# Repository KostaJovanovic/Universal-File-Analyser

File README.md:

## Download the apps

[Download stable release](https://github.com/KostaJovanovic/Universal-File-Analyser/releases/latest)

<div align="center">

# Analyser

**A zero-backend forensic workbench for files, running entirely in your browser.**

Drop in any file and it is classified, parsed and visualised on your device. Nothing is uploaded, ever.

[**Open Analyser**](https://analyser.valjdakosta.com) · [Supported formats](https://analyser.valjdakosta.com/formats) · [Samples](https://analyser.valjdakosta.com/samples) · [About](https://analyser.valjdakosta.com/about) · [Changelog](https://analyser.valjdakosta.com/patch)

</div>

---

## Download the apps

[Download stable release](https://github.com/KostaJovanovic/Universal-File-Analyser/releases/latest)

## Why

Most "file inspector" sites work by uploading your file to a server, which is exactly what you do not want for private photos, contracts, disk images or key files. Analyser takes the opposite approach: the page is static, there is no backend at all, and every byte of analysis happens in your browser through the File API and lazy-loaded WebAssembly. It works offline as an installable PWA, and you can verify the no-upload claim with the network tab open.

## What it can open

Analyser recognises **over 1,350 file types**. The depth varies by format: photos, audio, video, documents, 3D models, archives, maps and databases get full viewers and deep analysis, while hundreds of proprietary formats are identified by magic bytes with their header metadata decoded. Anything still unknown gets a hex dump and best-effort identification.

The full, searchable list is at [analyser.valjdakosta.com/formats](https://analyser.valjdakosta.com/formats), with a guide page for every supported extension. There is also a [compare page](https://analyser.valjdakosta.com/compare) that runs two files through the same analysis side by side and highlights every field where they differ, and a [samples gallery](https://analyser.valjdakosta.com/samples) of example files to try without needing your own.

## Beyond identification

Identifying a file is just the entry point. The real work starts once Analyser knows what it is holding, and a lot of that is best shown rather than described.

### Audio: spectrograms, isolation and on-device AI

Waveform and spectrogram views (down into the sub-20 Hz range), codec and loudness analysis, reversed playback, and live microphone capture. The frequency-isolation panel lets you carve out bands in real time, and an in-browser AI model separates vocals from instrumentals with no server round-trip.

<div align="center">

</div>

<div align="center">

https://github.com/user-attachments/assets/a9226e4a-90d0-45d2-8c82-d65578e2b3e8

<em>On-device AI vocal separation: the model runs entirely in the browser, nothing is uploaded.</em>

</div>

### 3D, CAD and manufacturing

STL and STEP/IGES viewers, DWG drawings, SolidWorks and Fusion 360 packages, and a G-code toolpath simulator that rebuilds the print as solid deposited filament, animates the build layer by layer, and can export a shareable video clip of it.

<div align="center">

</div>

### Electronics

KiCad and Altium PCB projects render as an interactive 3D board you can flip and inspect, alongside schematics, SPICE waveforms and IPC netlists.

<div align="center">

</div>

### Creative project files

After Effects, Premiere, DaVinci Resolve and VEGAS projects with previewable composition timelines, EDL/FCPXML/OTIO timelines, PSD and Illustrator files, colour LUTs, animated font specimens, Lottie animations, MIDI scores, subtitles and lyrics.

<div align="center">

</div>

### Folders and archives

Browse ZIP, 7z, RAR and whole dropped folders, with a treemap that breaks down where the size actually goes and lets you click straight into any file to analyse it. Comics (CBZ/CBR), e-books (EPUB/MOBI), DjVu scans and Jupyter notebooks get proper readers.

<div align="center">

</div>

### And more

- **File recovery** - repair truncated or corrupt JPEG/PNG files, rebuild a damaged JPEG header using a reference photo from the same camera, carve embedded images out of any blob, and salvage unfinalised MP4/MOV recordings with no index by extracting the raw H.264/H.265 stream (with a reference clip as donor if needed).
- **Photos** - EXIF and GPS readout, histograms, OCR, QR-code detection, HEIC and camera-RAW conversion, and a "sonify" mode that turns the image into sound.
- **Video** - per-frame and stream analysis, scene-change detection, and scrubbing synced between the player and the readouts.
- **Forensics and data** - CRC-32, MD5, SHA-1, SHA-256 and SHA-512 hashes, a network-indicator (OSINT) card that pulls URLs, IPs, domains and emails out of any file into click-to-open lookup links (nothing is contacted automatically), plus viewers for SQLite databases, git objects, emails and disk images, and a JSON export of the full analysis.
- **Geodata** - GPX tracks, KML and GeoJSON plotted on a map, rendered locally.

## Privacy

- No uploads: files are read with the File API and never leave the device.
- No accounts, no trackers, ZERO tracking cookies. The only thing counted is an anonymous per-extension tally (see the privacy page).
- Works fully offline once installed; the service worker precaches the app shell and keeps the WASM engines after first use.
- Private keys and secrets found inside files are flagged, not transmitted.

The only network call the site ever makes on its own is a single anonymous "file analysed" ping carrying nothing but a lowercase extension string. Those counts feed the public [live-usage page](https://analyser.valjdakosta.com/stats), an honest tally of what people drop, with unrecognised types pooled into one row so their names are never shown or stored.

<div align="center">

</div>

## Style

You have probably never seen a file analysis website this stylish. It follows a [swiss design](https://en.wikipedia.org/wiki/Swiss_Style_(design)) inspired layout, colour palette and set of fonts which I am very happy with. I made sure to sacrifice no functionality or readability for the sake of being cool, and hopefully succeeded in that too. Sharp corners, mono type, no clutter. And a... hidden game?

<div align="center">

</div>

## Under the hood

The site is plain HTML, CSS and ES-module JavaScript. No framework, no build step, no `node_modules`. Heavy lifting is done by WebAssembly engines and specialist libraries, loaded lazily only when a file actually needs them:

- **FFmpeg** for video remuxing, frame extraction and audio decoding
- **ImageMagick** for RAW photo conversion
- **pdf.js** and **Ghostscript** for PDF and PostScript
- **Tesseract** for OCR
- **OpenCASCADE** for STEP/IGES tessellation (fetched on first use, then cached for offline)
- **sql.js** for SQLite, **libarchive** and **xz** for archives, **OpenJPEG** for JPEG 2000
- **exifr**, **heic2any**, **jsQR**, **Leaflet**, **fflate** and friends

Most parsing, though, is hand-written: a couple of hundred binary header parsers organised into lazy per-domain chunks, so the initial page stays small. Deployment is just static assets on Cloudflare; every push to `main` ships.

## Offline install

The "Download for offline use" section in the footer caches Analyser as an installable, fully offline Progressive Web App, in three cumulative tiers: **Essentials** (the whole app), **Everything** (adds OCR, maps, QR scanning, HEIC, archives, PostScript, CAD drawings and the samples gallery) and **Complete** (OCR in 30+ languages plus the on-device AI vocal separation).

<div align="center">

</div>

## Desktop app

Analyser also runs as a desktop application for Windows, macOS and Linux. It wraps the same `web/` tree the site serves, so there is no fork of the code and nothing in the analysis pipeline changes - and the privacy promise is identical, since everything still happens on your own machine.

The source is in `desktop/` (Electron, its own `package.json`). Build the Windows installer locally with `cd desktop && npm install && npm run dist`, which writes `Analyser-Windows-<version>.exe` into `desktop/dist/`. That one file installs Analyser or unpacks a portable copy. The desktop adds File > Open and Open folder, opens files handed to it from Explorer or the command line, sizes its memory limits from real RAM rather than the browser's clamped figure, and saves the exported report through a native dialog. See [`desktop/README.md`](desktop/README.md) and [the docs page](https://analyser.valjdakosta.com/docs/desktop).

## Android app

An Android app is in development, built the same way as the desktop one: a Capacitor shell around the same `web/` tree, with no fork of the code. On top of the website it adds "Open with" and "Share to Analyser", a native save for every download, and a real FFmpeg binary that encodes video on the phone's own hardware (MediaCodec). Early builds are in the [latest release](https://github.com/KostaJovanovic/Universal-File-Analyser/releases/latest), and the app updates from there. The source is in `mobile/`; see [`mobile/README.md`](mobile/README.md) and [the docs page](https://analyser.valjdakosta.com/docs/mobile).

## Running locally

```
server.bat
```

This starts a local instance on localhost:3000 and opens it in a browser. It keeps 100% of the functionality since everything was built to be server-independent. The printed network URL also works for phone testing on the same Wi-Fi. There is nothing to install and nothing to build; editing a file and refreshing is the whole dev loop.

## Project layout

- `web/` - the entire website (served at the domain root); everything below lives here
- `web/index.html` - the drop-and-analyse app
- `web/assets/js/core/formats.js` - the single source of truth for every supported file type
- `web/assets/js/renderers/` - one module per top-level type (photo, audio, video, PDF, 3D, ...)
- `web/assets/js/parsers/` - lazy per-domain metadata parsers for the long tail of formats
- `web/assets/js/lib/` - shared binary helpers and WASM loaders
- `web/assets/vendor/` - third-party libraries, served locally so the app stays offline-capable
- `tools/` - Node scripts (in the repo root) that pre-render the `/formats` SEO pages from the catalog
- `worker/` - the Cloudflare Worker behind the anonymous analysed-file counter (the only server-side code)
- `desktop/` - the Electron desktop shell, which wraps the same `web/` tree
- `mobile/` - the Android shell (Capacitor), which wraps it too
- `web/sw.js` - the service worker behind the offline support

## Versioning

Every commit is its own version (currently in the 5.x era), stamped automatically at commit time. The full history, one entry per commit, is on the [changelog](https://analyser.valjdakosta.com/patch).

## Credits

The idea and need for this website was mine, originally made as a simple tool for generating spectrograms and reading a photo aspect ratio, that spiraled out of control pretty quickly. Many thanks to my parents, who encouraged me to continue by finding this cool, and to friends who tested this for me on platforms I do not possess or use frequently (Linux Arch and Debian, macOS). Since this project was made possible with Claude, and having in mind the moral and ethical dilemmas regarding AI usage, I decided to make the source available to the public.

## License

Copyright © 2026 Kosta. Licensed under the [GNU General Public License v3.0](LICENSE).

Analyser is free software: you are free to use, study, modify and share it, for any purpose including commercially. The condition is reciprocity, if you distribute it or a modified version, you must pass on the same freedoms, releasing your source under the GPL too. It comes with no warranty.

This licence covers the code I wrote. Third-party libraries under `web/assets/vendor/` remain under their own licences (Ghostscript under AGPL-3.0 and LibRaw under LGPL among them), each shipped with its licence alongside it and credited in the site footer.

## Documentation

For a deeper look at the codebase, architecture, the drop-to-render pipeline, every renderer module, and a full usage reference for every feature on the site, see [`analyser.valjdakosta.com/docs`](documentation).

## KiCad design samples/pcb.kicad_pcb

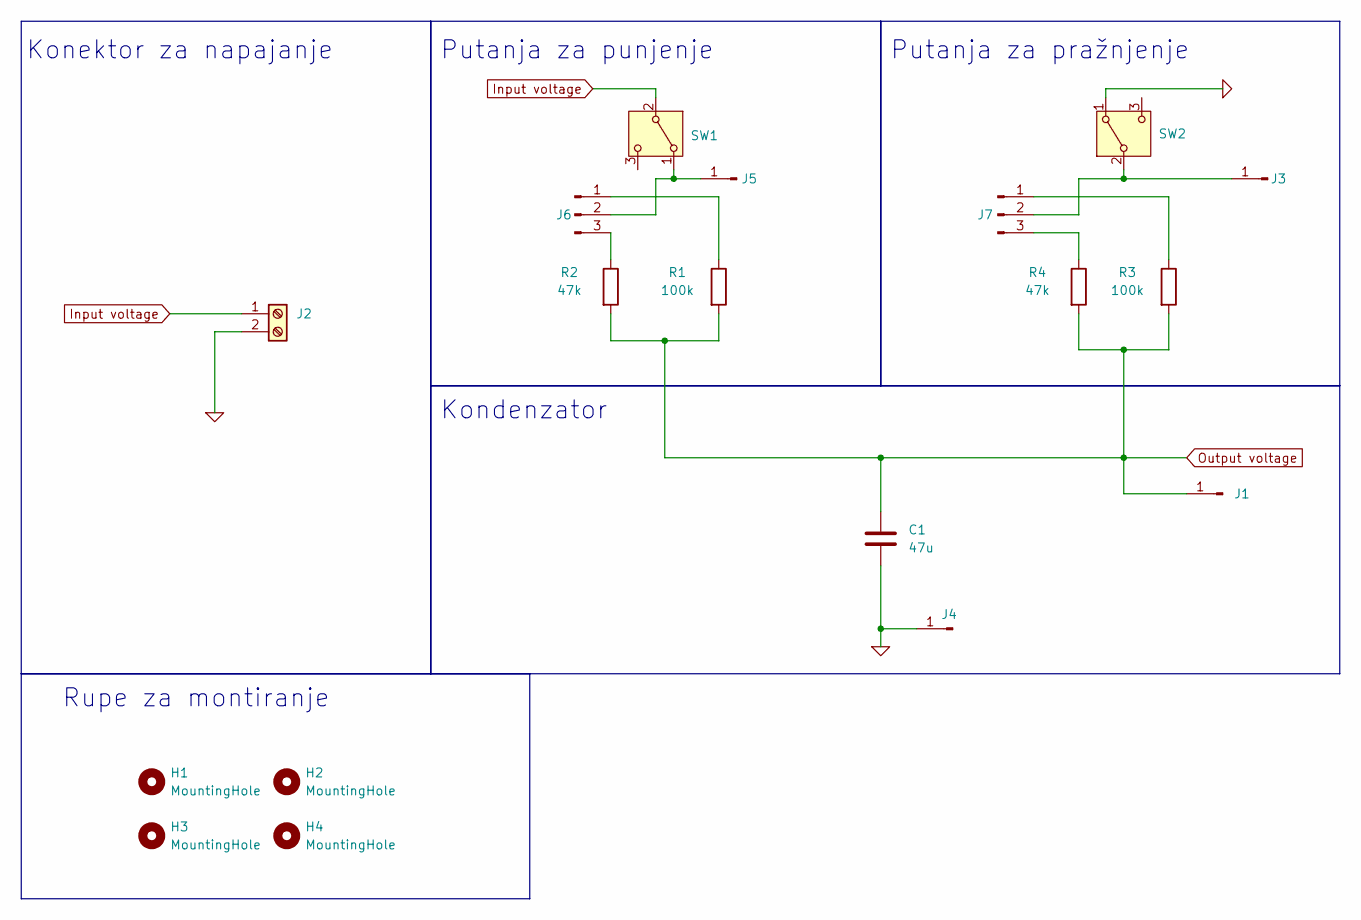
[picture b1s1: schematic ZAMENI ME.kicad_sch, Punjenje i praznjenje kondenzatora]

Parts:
C1: 47u; C_1206_3216Metric; LCSC C76659
H1, H2, H3, H4: MountingHole; MountingHole_3.2mm_M3_ISO14580_Pad_TopBottom
J1, J3, J4, J5: Conn_01x01_Pin; PinHeader_1x01_P2.54mm_Vertical
J2: Screw_Terminal_01x02; TerminalBlock_Phoenix_MKDS-1,5-2-5.08_1x02_P5.08mm_Horizont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
J6, J7: Conn_01x03_Pin; PinHeader_1x03_P2.54mm_Vertical
R1, R3: 100k; R_1206_3216Metric_Pad1.30x1.75mm_HandSolder; LCSC C17900
R2, R4: 47k; R_1206_3216Metric_Pad1.30x1.75mm_HandSolder; LCSC C25664
SW1, SW2: SW_SPDT; SW-TH_2MS1T1B1M1QES-5

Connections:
0: C1.2, J2.2, J4.1, SW2.1 (A)
Input voltage: J2.1, SW1.2 (B)
unnamed: J3.1, J7.2, SW2.2 (B)
unnamed: J5.1, J6.2, SW1.1 (A)
unnamed: J6.1, R1.1
unnamed: J6.3, R2.1
unnamed: J7.1, R3.1
unnamed: J7.3, R4.1
Output voltage: C1.1, J1.1, R1.2, R2.2, R3.2, R4.2

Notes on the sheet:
Rupe za montiranje
Kondenzator
Konektor za napajanje
Putanja za pražnjenje
Putanja za punjenje

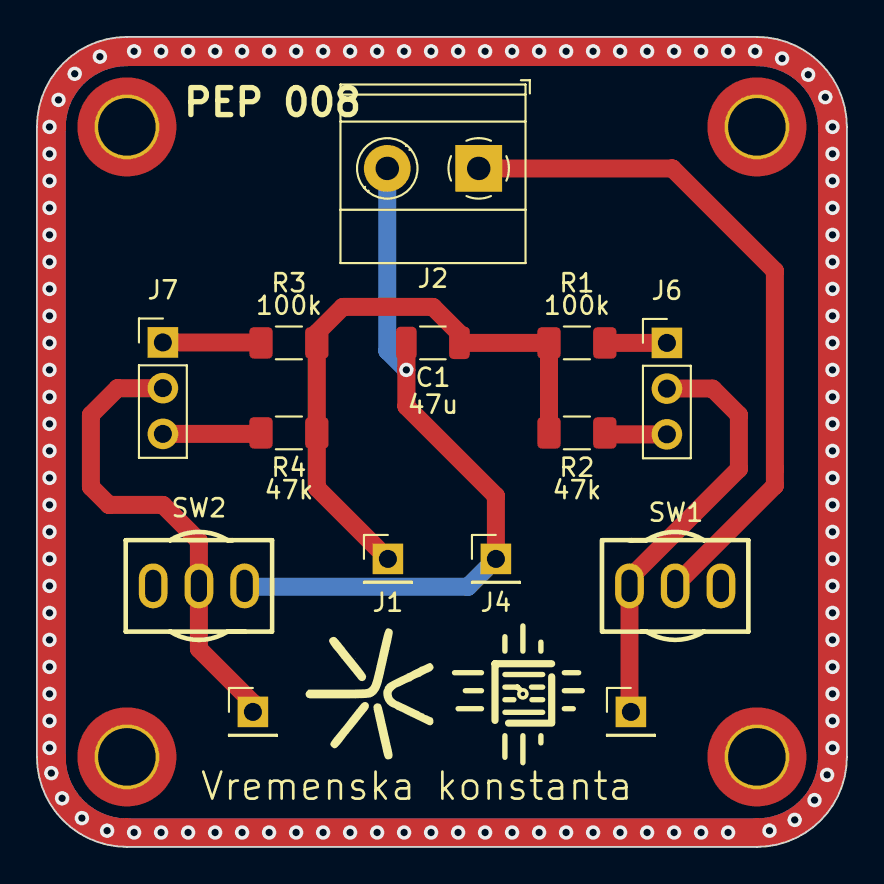
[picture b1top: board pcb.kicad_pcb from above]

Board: 2 copper layers, 45.0 x 45.0 mm, 18 parts (0 on the bottom side), 9 nets.

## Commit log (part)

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2026-06-25 pre release 5.0
